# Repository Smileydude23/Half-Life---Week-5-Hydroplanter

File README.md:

# Half-Life---Week-5-Hydroplanter
A plant waterer that uses moisture sensors to detect when the plant needs watering, then a pump will pump water from a bowl/bottle of water to the plant. The design was made in KiCad and the code was made in Arduino IDE. I made this project because my plant, Dusty, is in need of consistent watering and it suffers a lot from when I leave the house for extended periods of time, like when I am camping. The PCB is built around an ESP32-C3 microcontroller. It monitors soil moisture and water level, controls a pump through a MOSFET, manages battery charging and protection, and displays status information on an OLED. The wiring is really trash because I'm bad at wiring but it should work. The Arduino firmware I wrote monitors soil moisture and water-tank availability, displays the plant’s moisture level on an OLED screen, and automatically controls a pump. It starts watering when the soil moisture falls to 30% or below, stops at 55%, and includes safety limits for an empty tank, a 15-second maximum runtime, and a 10-minute delay between watering cycles. It also averages multiple soil-sensor readings, converts them into a 0–100% moisture value, and shows the plant graphic, status, and sensor data on the display.

Onshape Link:
https://cad.onshape.com/documents/5bbc0352c67ef33b2cdba1d2/w/0c9466e1c6beb604306bf71a/e/59fa4b2cb4097b58a1eba9d7?renderMode=0&uiState=6af141bfefa43e0b0855de01

## Bill of Materials

| Part | Qty | Unit Price (USD) | Total (USD) | Vendor |
| :--- | :---: | :---: | :---: | :--- |
| **1/4" Vinyl Tubing** <br> | 1 | $3.83 | $3.83 | Temu |
| **0.96-inch OLED Display Module I2C** <br> | 1 | $1.98 | $1.98 | Temu |
| **2pcs/lot 18650 Battery Case** <br> | 1 | $1.44 | $1.44 | Temu |
| **MF-RHT050-0** <br> | 2 | $1.87 | $3.74 | Digikey |
| **SS14** <br> | 3 | $1.38 | $4.14 | Digikey |
| **USB4125-GF-A** <br> | 1 | $0.64 | $0.64 | Digikey |
| **IRLZ44NPBF** <br> | 1 | $2.02 | $2.02 | Digikey |
| **FS8205A** <br> | 1 | $0.69 | $0.69 | Digikey |
| **MFR-25FTF52-1K5** <br> | 2 | $0.21 | $0.42 | Digikey |
| **MFR-25FBF52-732K** <br> | 1 | $0.11 | $0.11 | Digikey |
| **DW01A** <br> | 1 | $0.11 | $0.11 | Digikey |
| **BQ24074RGTR** <br> | 1 | $2.73 | $2.73 | Digikey |
| **SMD IC MT3608** <br> | 1 | $0.29 | $0.29 | Digikey |
| **K104K15X7RF53L2** <br> | 2 | $0.57 | $1.14 | Digikey |
| **FK22X7R1E475K0000** <br> | 1 | $1.63 | $1.63 | Digikey |
| **S3B-PH-K-S** <br> | 1 | $0.16 | $0.16 | Digikey |
| **S2B-PH-K-S** <br> | 2 | $0.26 | $0.52 | Digikey |
| **78F4R7J-RC** <br> | 1 | $0.25 | $0.25 | Digikey |
| **I13991054** <br> | 1 | $1.21 | $1.21 | Aliexpress |
| **SEN0193** <br> | 1 | $6.21 | $6.21 | Digikey |
| **4547** <br> | 1 | $3.31 | $3.31 | Digikey |
| **PLS-03IA-3PAI** <br> | 1 | $3.19 | $3.19 | Digikey |
| **50YXJ22MTA5X11** <br> | 1 | $0.28 | $0.28 | Digikey |
| **PCB Manufacturing** <br> | 1 | $4.00 | $4.00 | JLCPCB |
| **Tax & shipping** <br> | — | — | $17.08 | — |
| **Total Funding Used** | — | — | **$61.12 / $65** | |

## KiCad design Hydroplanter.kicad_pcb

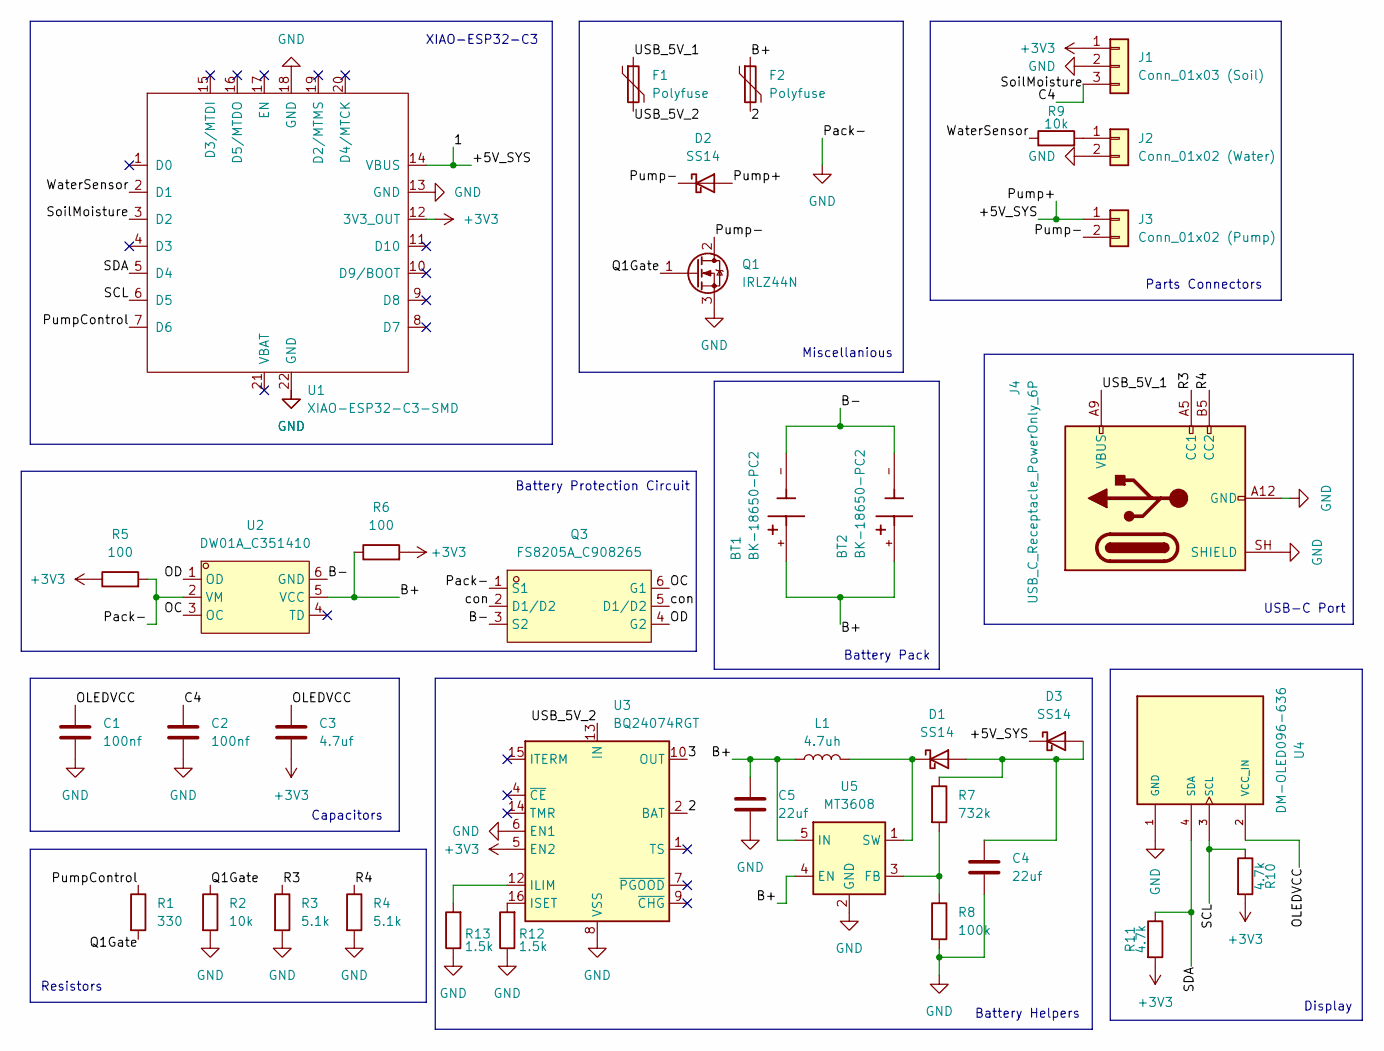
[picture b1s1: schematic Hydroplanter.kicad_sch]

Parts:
BT1, BT2: BK-18650-PC2; BAT_BK-18650-PC2; MPN BK-18650-PC2
C1, C2: 100nf; C_Disc_D5.0mm_W2.5mm_P5.00mm
C3: 4.7uf; C_Disc_D5.0mm_W2.5mm_P5.00mm
C4, C5: 22uf; C_Disc_D5.0mm_W2.5mm_P5.00mm
D1, D2, D3: SS14; D_SMA
F1, F2: Polyfuse; Fuse_Bourns_MF-RHT050
J1: Conn_01x03 (Soil); PhoenixContact_GMSTBA_2,5_3-G-7,62_1x03_P7.62mm_Horizontal
J2: Conn_01x02 (Water); PhoenixContact_GMSTBA_2,5_2-G_1x02_P7.50mm_Horizontal
J3: Conn_01x02 (Pump); PhoenixContact_GMSTBA_2,5_2-G_1x02_P7.50mm_Horizontal
J4: USB_C_Receptacle_PowerOnly_6P; USB_C_Receptacle_GCT_USB4125-xx-x-0190_6P_TopMnt_Horizontal
L1: 4.7uh; L_Axial_L7.0mm_D3.3mm_P10.16mm_Horizontal_Fastron_MICC
Q1: IRLZ44N; TO-220-3_Vertical
Q3: FS8205A_C908265; SOT-23-6_L2.9-W1.6-P0.95-LS2.8-BR; MPN FS8205A; LCSC Part C908265
R1: 330; R_Axial_DIN0207_L6.3mm_D2.5mm_P7.62mm_Horizontal
R2, R9: 10k; R_Axial_DIN0207_L6.3mm_D2.5mm_P7.62mm_Horizontal
R3, R4: 5.1k; R_Axial_DIN0207_L6.3mm_D2.5mm_P7.62mm_Horizontal
R5, R6: 100; R_Axial_DIN0207_L6.3mm_D2.5mm_P7.62mm_Horizontal
R7: 732k; R_Axial_DIN0207_L6.3mm_D2.5mm_P7.62mm_Horizontal
R8: 100k; R_Axial_DIN0207_L6.3mm_D2.5mm_P7.62mm_Horizontal
R10, R11: 4.7k; R_Axial_DIN0207_L6.3mm_D2.5mm_P7.62mm_Horizontal
R12, R13: 1.5k; R_Axial_DIN0207_L6.3mm_D2.5mm_P7.62mm_Horizontal
U1: XIAO-ESP32-C3-SMD
U2: DW01A_C351410; SOT-23-6_L2.9-W1.6-P0.95-LS2.8-BL; MPN DW01A; LCSC Part C351410
U3: BQ24074RGT; VQFN-16-1EP_3x3mm_P0.5mm_EP1.6x1.6mm
U4: DM-OLED096-636; MODULE_DM-OLED096-636; MPN DM-OLED096-636
U5: MT3608; SOT-23-6

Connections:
+3V3: C3.2, J1.1, R5.1, R6.2, R10.2, R11.2, U1.12 (3V3_OUT), U3.5 (EN2)
/2: F2.2, U3.2 (BAT), U3.3 (BAT)
/3: U3.10 (OUT), U3.11 (OUT)
/+5V_SYS: D2.2 (A), D3.1 (K), J3.1, U1.14 (VBUS)
/B+: BT1.+, BT2.+, C5.1, F2.1, L1.1, R6.1, U2.5 (VCC), U5.4 (EN), U5.5 (IN)
/B-: BT1.-, BT2.-, Q3.3 (S2), U2.6 (GND)
/C4: C2.1, J1.3, U1.3 (D2)
/OC: Q3.6 (G1), U2.3 (OC)
/OD: Q3.4 (G2), U2.1 (OD)
/OLEDVCC: C1.1, C3.1, U4.2 (VCC_IN)
/Pump-: D2.1 (K), J3.2, Q1.2 (D)
/PumpControl: R1.1, U1.7 (D6)
/Q1Gate: Q1.1 (G), R1.2, R2.1
/R3: J4.A5 (CC1), R3.1
/R4: J4.B5 (CC2), R4.1
/SCL: R10.1, U1.6 (D5), U4.3 (SCL)
/SDA: R11.1, U1.5 (D4), U4.4 (SDA)
/USB_5V_1: F1.1, J4.A9 (VBUS), J4.B9 (VBUS)
/USB_5V_2: F1.2, U3.13 (IN)
/WaterSensor: R9.1, U1.2 (D1)
/con: Q3.2 (D1/D2), Q3.5 (D1/D2)
GND: C1.2, C2.2, C4.2, C5.2, J1.2, J2.2, J4.A12 (GND), J4.B12 (GND), J4.SH (SHIELD), Q1.3 (S), Q3.1 (S1), R2.2, R3.2, R4.2, R5.2, R8.2, R12.1, R13.1, U1.13 (GND), U1.18 (GND), U1.22 (GND), U2.2 (VM), U3.6 (EN1), U3.8 (VSS), U3.17 (VSS), U4.1 (GND), U5.2 (GND)
unnamed: C4.1, D1.2 (A), D3.2 (A), R7.1
unnamed: D1.1 (K), L1.2, U5.1 (SW)
unnamed: J2.1, R9.2
unnamed: R13.2, U3.12 (ILIM)
unnamed: R12.2, U3.16 (ISET)
unnamed: R7.2, R8.1, U5.3 (FB)

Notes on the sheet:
Battery Pack
USB-C Port
XIAO-ESP32-C3
Resistors
Battery Protection Circuit
Miscellanious
Battery Helpers
Capacitors
Parts Connectors
Display

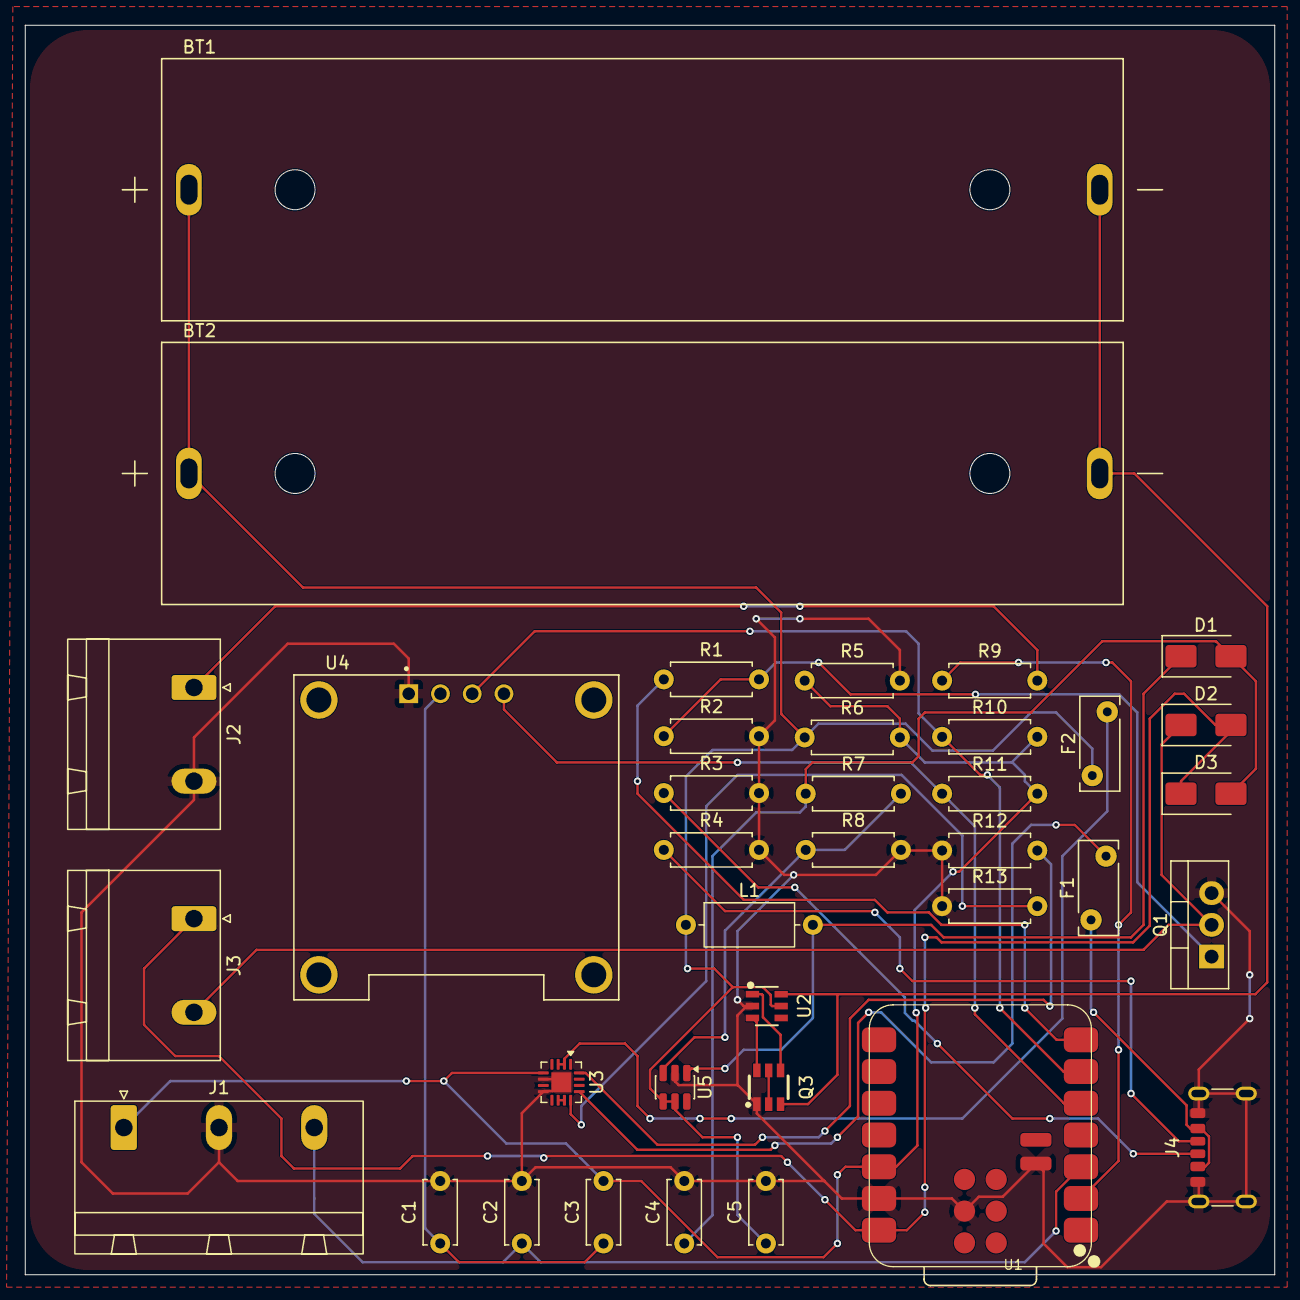
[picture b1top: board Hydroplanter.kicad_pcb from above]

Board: 2 copper layers, 100.0 x 100.0 mm, 37 parts (0 on the bottom side), 28 nets.
